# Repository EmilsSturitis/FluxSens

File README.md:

# FluxSens
Breakout board for DRV  
## 📘 Overview

This project is a small breakout for a DRV5053RA

Designed for use in development of my Master thesis about non-invasive current measurments. It emphasizes **small size** and **adaptability** for placement of sensors in the development.

---

## ⚙️ Hardware Specifications

| Component | Function | Notes |
|------------|-----------|-------|
| **DRV5053RA** | Sensor | -45mV/mT |

---

📂 Related Resources
* **Helpful Resources:**
    * [DRV5035 Datasheet](https://www.ti.com/lit/ds/symlink/drv5053.pdf?ts=1762341356613&ref_url=https%253A%252F%252Fwww.google.com%252F)

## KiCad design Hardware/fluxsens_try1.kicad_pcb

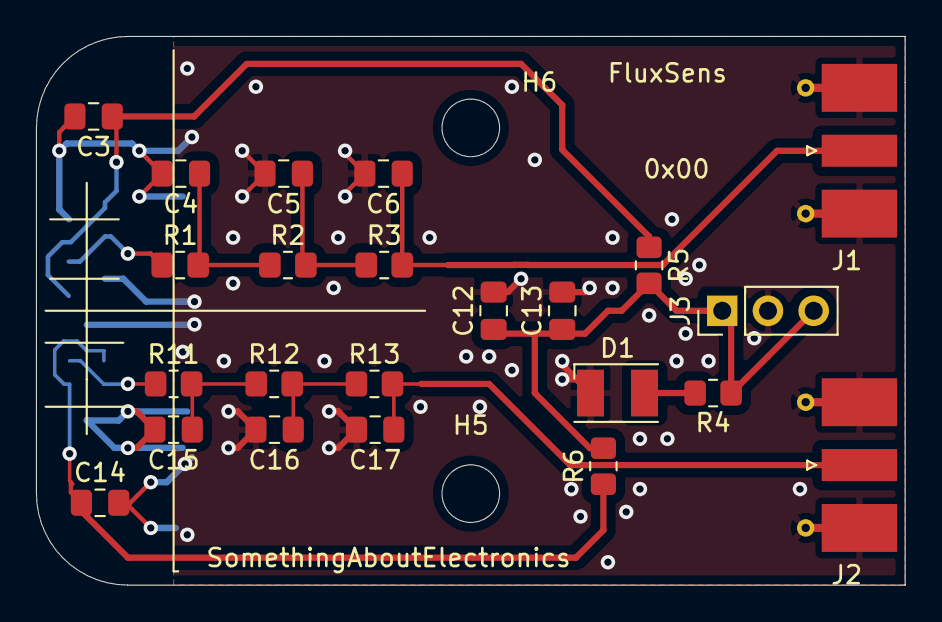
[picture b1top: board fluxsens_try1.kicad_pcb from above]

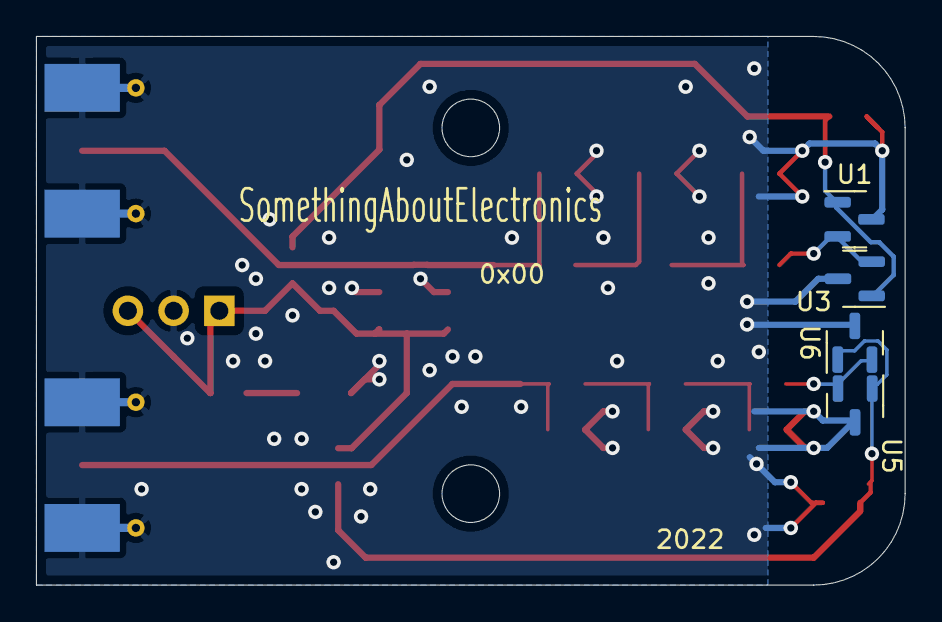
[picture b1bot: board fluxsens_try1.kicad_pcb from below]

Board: 2 copper layers, 48.3 x 30.5 mm, 29 parts (4 on the bottom side), 13 nets.

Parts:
C3, C4, C5, C6, C12, C13, C14, C15, C16, C17: C_Small; C_0805_2012Metric_Pad1.18x1.45mm_HandSolder
D1: LED_Small; LED_PLCC-2
H5, H6: MountingHole; MountingHole_3.2mm_M3_DIN965
J1, J2: Conn_Coaxial; SMA_Molex_73251-2120_EdgeMount_Horizontal
J3: Conn_01x03; PinHeader_1x03_P2.54mm_Vertical
R1, R2, R3, R4, R5, R6, R11, R12, R13: R_Small; R_0805_2012Metric_Pad1.20x1.40mm_HandSolder
U1, U3, U5, U6: DRV5033AJQDBZ; SOT-23

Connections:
+3V3: C12.1, C13.1, J3.1, J3.3, R4.1, R5.2, R6.2
/V_out: C6.1, J1.1 (In), R3.2
/V_out_2: C17.1, J2.1 (In), R13.2
GND: C3.2, C4.2, C5.2, C6.2, C12.2, C13.2, C14.2, C15.2, C16.2, C17.2, D1.1 (K), J1.2 (Ext), J2.2 (Ext), J3.2, U1.3 (GND), U3.3 (GND), U5.3 (GND), U6.3 (GND)
unnamed: C3.1, R5.1, U1.1 (VCC), U3.1 (VCC)
unnamed: C4.1, R1.2, R2.1
unnamed: C5.1, R2.2, R3.1
unnamed: C14.1, R6.1, U5.1 (VCC), U6.1 (VCC)
unnamed: C15.1, R11.2, R12.1
unnamed: C16.1, R12.2, R13.1
unnamed: D1.2 (A), R4.2
unnamed: R1.1, U1.2 (VOUT), U3.2 (VOUT)
unnamed: R11.1, U5.2 (VOUT), U6.2 (VOUT)

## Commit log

2022-12-08 changeover from Kicad V5 to V6
2025-11-05 Update KiCad project files and add PCB markings
    Updated .gitignore to exclude .zip files. Modified KiCad project, schematic, and settings files with new configuration and metadata. Added PCB markings image to Media directory. Lock files for KiCad 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
2025-11-05 Update README and add schematic snippet image
    Revised README to reflect use of DRV5053RA sensor and updated project context for Master thesis development. Replaced component and pinout tables with simplified sensor info and added a new schematic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
